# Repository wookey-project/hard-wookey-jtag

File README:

# WooKey JTAG Flasher PCB

## Introduction

Wookey | https://wookey-project.github.io/
Copyright 2018 The wookey project team <wookey@ssi.gouv.fr>

The Wookey from [ANSSI](https://www.ssi.gouv.fr) is an open source
hardware design, implementing an Encrypted Flash Drives.

This repository is aimed towards developers.

### Revision information

This directory contains the hardware design for the Wookey board, first public version (Wookey V2).

### PCB editing tools

All PCB files (schematic and PCB layout) have been designed using the KiCad EDA.
This Cross Platform and Open Source Electronics Design Automation Suite can be downloaded
on http://kicad-pcb.org/.

## Production files generation 101

### Configure the project

KiCad binaries location may change regarding your operating system.
This is why you have to set your environment.
This is done by sourcing the `setenv.sh` script. This script exports
all paths that are required in order to automaticaly generate the production files.

Most of the time, the paths proposed in this script are not the one you use in your specific installation.
The `setenv.sh` script support easy variables overloading by including a `setenv.local.sh` script file if this file exists in the same directory.
If you need to overload some of the variables of the `setenv.sh` script, just add them to your own `setenv.local.sh` file.
Here is an example to define KiCad environement path on Apple Mac OS.

```
  $ echo "export PYTHON_BIN_PATH = /Applications/KiCad/kicad.app/Contents/Frameworks/Python.framework/Versions/2.7/bin/python" > setenv.local.sh
  $ source setenv.sh
  Loading local SDK settings...
  =========================================================
  === Kicad environment configuration
  =========================================================
  PYTHON_BIN_PATH   = /Applications/KiCad/kicad.app/Contents/Frameworks/Python.framework/Versions/2.7/bin/python
  PYTHON_PATH     = /Applications/Kicad/kicad.app/Contents/Frameworks/python/site-packages
  BOM_GEN_PATH = /Applications/Kicad/kicad.app/Contents/SharedSupport/plugins/bom2grouped_csv.xsl
  TOOLS_PATH = ../../../tools
  =========================================================
```

The production files can be generated using the following command.

```
$ make
```

This will generate the production files in a new sub directory.
The directory name may differ according the project your are working with.

## PCB Pinout

## PCB Layers

### PCB TOP layer

### PCB BOTTOM layer

### Layers

Order and type of copper layers:
  TOP:  signal, front components
  GND:  ground plane
  PWR:  ground and power plane
  BOT:  signal, back components

### Stackup
4 layers, 1.6mm thickness
Outer layers 1 oz base copper foil
Inner layers 0.5 oz base copper foil

Electroless Nickel Immersion Gold (ENIG) surface finish

solder resist   0.0254mm
copper          0.0356mm    L1 (TOP)
FR408 prepreg   0.1702mm
copper          0.0178mm    L2 (GND)
FR408           1.1938mm
copper          0.0178mm    L3 (PWR)
FR408 prepreg   0.1702mm
copper          0.0356mm    L4 (BOT)
solder resist   0.0254mm

The substrate for both the core and prepreg is FR408,
with a dielectric constant of 3.66 at 1GHz.
The prepreg is comprised of 2 layers of Isola 2113.

## Regulatory compliance & handling

The Wookey board is intended for use as a development platform for hardware
or software. The board is an open system design, which does not include a
shielded enclosure. This may cause interference to other electrical or
electronic devices in close proximity. In a domestic environment, this product
may cause radio interference in which case the user may be required to take
adequate measures. In addition, this board should not be used near any medical
equipment or RF devices.

The board is sensitive to ESD. Hold the board only by its edges. After removing
the board from its box, place it on a grounded, static-free surface.

The board can become hot, like any fan-less design, during continuous high CPU
loads, mind its temperature while handling it.

## License

Wookey | https://wookey-project.github.io/
Copyright 2018 The wookey project team <wookey@ssi.gouv.fr>

This is an open hardware design licensed under the terms of the CERN Open
Hardware Licence (OHL) v1.2.

You may redistribute and modify this documentation under the terms of the CERN
OHL v.1.2 (http://ohwr.org/cernohl). This documentation is distributed WITHOUT
ANY EXPRESS OR IMPLIED WARRANTY, INCLUDING OF MERCHANTABILITY, SATISFACTORY
QUALITY AND FITNESS FOR A PARTICULAR PURPOSE. Please see the CERN OHL v.1.2 for
applicable conditions.

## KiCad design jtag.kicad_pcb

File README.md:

# WooKey JTAG Flasher PCB

## Introduction

Wookey | https://wookey-project.github.io/
Copyright 2018 ANSSI

Authors: The Wookey project Team <wookey@ssi.gouv.fr>

The Wookey from [ANSSI](https://www.ssi.gouv.fr) is an open source
hardware design, implementing an Encrypted Flash Drives.

This repository is aimed towards developers.

### Revision information

This directory contains the hardware design for the Wookey board, first public version (Wookey V2).

### PCB editing tools

All PCB files (schematic and PCB layout) have been designed using the KiCad EDA.
This Cross Platform and Open Source Electronics Design Automation Suite can be downloaded
on http://kicad-pcb.org/.

## Production files generation 101

### Configure the project

KiCad binaries location may change regarding your operating system.
This is why you have to set your environment.
This is done by sourcing the `setenv.sh` script. This script exports
all paths that are required in order to automaticaly generate the production files.

Most of the time, the paths proposed in this script are not the one you use in your specific installation.
The `setenv.sh` script support easy variables overloading by including a `setenv.local.sh` script file if this file exists in the same directory.
If you need to overload some of the variables of the `setenv.sh` script, just add them to your own `setenv.local.sh` file.
Here is an example to define KiCad environement path on Apple Mac OS.

```
  $ echo "export PYTHON_BIN_PATH = /Applications/KiCad/kicad.app/Contents/Frameworks/Python.framework/Versions/2.7/bin/python" > setenv.local.sh
  $ source setenv.sh
  Loading local SDK settings...
  =========================================================
  === Kicad environment configuration
  =========================================================
  PYTHON_BIN_PATH   = /Applications/KiCad/kicad.app/Contents/Frameworks/Python.framework/Versions/2.7/bin/python
  PYTHON_PATH     = /Applications/Kicad/kicad.app/Contents/Frameworks/python/site-packages
  BOM_GEN_PATH = /Applications/Kicad/kicad.app/Contents/SharedSupport/plugins/bom2grouped_csv.xsl
  TOOLS_PATH = ../../../tools
  =========================================================
```

The production files can be generated using the following command.

```
$ make
```

This will generate the production files in a new sub directory.
The directory name may differ according the project your are working with.

## PCB Pinout

## PCB Layers

### PCB TOP layer

### PCB BOTTOM layer

### Layers

Order and type of copper layers:
  TOP:  signal, front components
  GND:  ground plane
  PWR:  ground and power plane
  BOT:  signal, back components

### Stackup
4 layers, 1.6mm thickness
Outer layers 1 oz base copper foil
Inner layers 0.5 oz base copper foil

Electroless Nickel Immersion Gold (ENIG) surface finish

solder resist   0.0254mm
copper          0.0356mm    L1 (TOP)
FR408 prepreg   0.1702mm
copper          0.0178mm    L2 (GND)
FR408           1.1938mm
copper          0.0178mm    L3 (PWR)
FR408 prepreg   0.1702mm
copper          0.0356mm    L4 (BOT)
solder resist   0.0254mm

The substrate for both the core and prepreg is FR408,
with a dielectric constant of 3.66 at 1GHz.
The prepreg is comprised of 2 layers of Isola 2113.

## Regulatory compliance & handling

The Wookey board is intended for use as a development platform for hardware
or software. The board is an open system design, which does not include a
shielded enclosure. This may cause interference to other electrical or
electronic devices in close proximity. In a domestic environment, this product
may cause radio interference in which case the user may be required to take
adequate measures. In addition, this board should not be used near any medical
equipment or RF devices.

The board is sensitive to ESD. Hold the board only by its edges. After removing
the board from its box, place it on a grounded, static-free surface.

The board can become hot, like any fan-less design, during continuous high CPU
loads, mind its temperature while handling it.

## License

Wookey | https://wookey-project.github.io/
Copyright 2018 ANSSI

Authors: The Wookey project Team <wookey@ssi.gouv.fr>

This is an open hardware design licensed under the terms of the CERN Open
Hardware Licence (OHL) v1.2.

You may redistribute and modify this documentation under the terms of the CERN
OHL v.1.2 (http://ohwr.org/cernohl). This documentation is distributed WITHOUT
ANY EXPRESS OR IMPLIED WARRANTY, INCLUDING OF MERCHANTABILITY, SATISFACTORY
QUALITY AND FITNESS FOR A PARTICULAR PURPOSE. Please see the CERN OHL v.1.2 for
applicable conditions.

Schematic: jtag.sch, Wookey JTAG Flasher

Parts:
C9001, C9003: 10uF; C_0603_1608Metric; MFG Part Num TP8M106M6R3C
C9002, C9004, C9005, C9006, C9007, C9008, C9009, C9010, C9011, C9012, C9013, C9014: 100nF; C_0603_1608Metric; MFG Part Num GRM188R71H104KA93D
D9002: LED BLUE; LED_0603_1608Metric_Castellated; MFG Part Num VLMB1300-GS08
J9001: USB; USB_A_CNCTech_1001-011-01101_Horizontal
J9002: Conn_01x03; PinHeader_1x02_P2.54mm_Vertical
J9003: JTAG; PinHeader_2x05_P2.54mm_Horizontal
P9001: DEBUG/PROG; PinHeader_1x06_P2.54mm_Vertical; MFG Part Num 90120-0766
R9001, R9002, R9004: 10K; R_0603_1608Metric
R9003: 470; R_0603_1608Metric
SW9001: DFU; KSR_TACTILE_SWITCH; MFG Part Num KSR231G LFS
TP9001: MSWDIO; TestPoint_Pad_D1.0mm
TP9002: MSWCLK; TestPoint_Pad_D1.0mm
TP9003: +3V3; TestPoint_Pad_D1.0mm
TP9004: GND; TestPoint_Pad_D1.0mm
TP9005: CAN1_RX; TestPoint_Pad_D1.0mm
TP9006: CAN1_TX; TestPoint_Pad_D1.0mm
TP9007: CAN2_RX; TestPoint_Pad_D1.0mm
TP9008: CAN2_TX; TestPoint_Pad_D1.0mm
U9001: LD1117S33TR; SOT-223; MFG Part Num LD1117S33TR
U9002: STM32F105RBTx; LQFP-64_10x10mm_P0.5mm
U9003, U9004, U9005: 74LVCH2T45DC; VSSOP-8_2.3x2mm_P0.5mm

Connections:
+3V3: C9003.1, C9004.1, C9005.1, C9006.1, C9007.1, C9008.1, C9009.1, C9010.1, C9014.1, P9001.2, R9004.1, SW9001.1, TP9003.1, U9001.2 (VO), U9002.1 (VBAT), U9002.13 (VDDA), U9002.19 (VDD), U9002.32 (VDD), U9002.48 (VDD), U9002.64 (VDD), U9003.1 (VCCA), U9004.8 (VCCB), U9005.8 (VCCB)
+5V: C9001.1, C9002.1, J9001.1 (VBUS), U9001.3 (VI), U9002.42 (PA9)
/BOOT0: R9002.1, SW9001.2, U9002.60 (BOOT0)
/BOOT1: R9001.1, U9002.28 (PB2)
/CAN1_RX: TP9005.1, U9002.61 (PB8)
/CAN1_TX: TP9006.1, U9002.62 (PB9)
/CAN2_RX: TP9007.1, U9002.33 (PB12)
/CAN2_TX: TP9008.1, U9002.34 (PB13)
/JTAG_DIR: U9002.15 (PA1), U9003.5 (DIR), U9004.5 (DIR), U9005.5 (DIR)
/JTAG_NRESET: U9002.16 (PA2), U9004.6 (2B)
/JTAG_OUT_TCK: J9003.4 (SWDCLK/TCK), U9003.6 (2B)
/JTAG_OUT_TDI: J9003.8 (NC/TDI), U9004.2 (1A)
/JTAG_OUT_TDO: J9003.6 (SWO/TDO), U9005.2 (1A)
/JTAG_OUT_TMS: J9003.2 (SWDIO/TMS), U9003.7 (1B)
/JTAG_OUT_TRESET: J9003.10 (~RESET~), U9004.3 (2A)
/JTAG_TCK: U9002.21 (PA5), U9003.3 (2A)
/JTAG_TDI: U9002.17 (PA3), U9004.7 (1B)
/JTAG_TDO: U9002.22 (PA6), U9005.7 (1B)
/JTAG_TMS: U9002.20 (PA4), U9003.2 (1A)
/JTAG_VREF: C9011.1, C9012.1, C9013.1, J9003.1 (VCC), U9003.8 (VCCB), U9004.1 (VCCA), U9005.1 (VCCA)
/LED1: R9003.1, U9002.29 (PB10)
/MCU_SWCLK: TP9002.1, U9002.49 (PA14)
/MCU_SWDIO: TP9001.1, U9002.46 (PA13)
/NRST: P9001.3, R9004.2, U9002.7 (NRST)
/RX: J9002.1, U9002.59 (PB7)
/SWCLK: P9001.4, U9002.38 (PC7)
/SWDIO: P9001.5, U9002.39 (PC8)
/SWO: P9001.6, U9002.55 (PB3)
/TX: J9002.2, U9002.58 (PB6)
/USB_FS_D+: J9001.3 (D+), U9002.45 (PA12)
/USB_FS_D-: J9001.2 (D-), U9002.44 (PA11)
GND: C9001.2, C9002.2, C9003.2, C9004.2, C9005.2, C9006.2, C9007.2, C9008.2, C9009.2, C9010.2, C9011.2, C9012.2, C9013.2, C9014.2, D9002.1 (K), J9001.4 (GND), J9001.5 (Shield), J9003.3 (GND), J9003.5 (GND), J9003.9 (GNDDetect), P9001.1, R9001.2, R9002.2, TP9004.1, U9001.1 (GND), U9002.12 (VSSA), U9002.18 (VSS), U9002.31 (VSS), U9002.47 (VSS), U9002.63 (VSS), U9003.4 (GND), U9004.4 (GND), U9005.4 (GND), U9005.6 (2B)
unnamed: D9002.2 (A), R9003.2

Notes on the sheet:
BOOT MODE
LED
POWER
Boot0 (1-2) = 0 => Flash memory aliased at 0x0000000

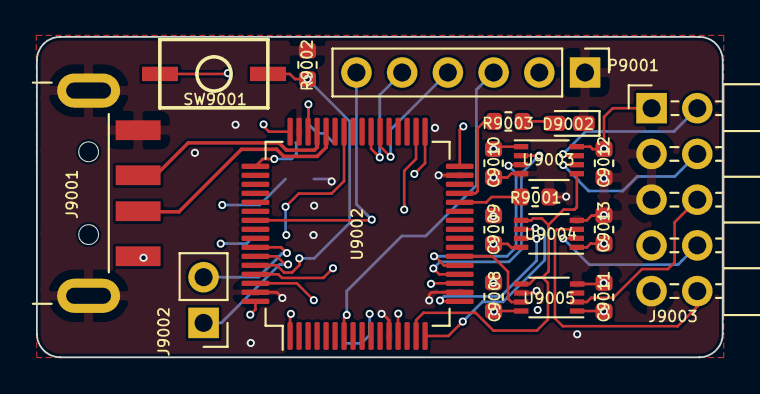
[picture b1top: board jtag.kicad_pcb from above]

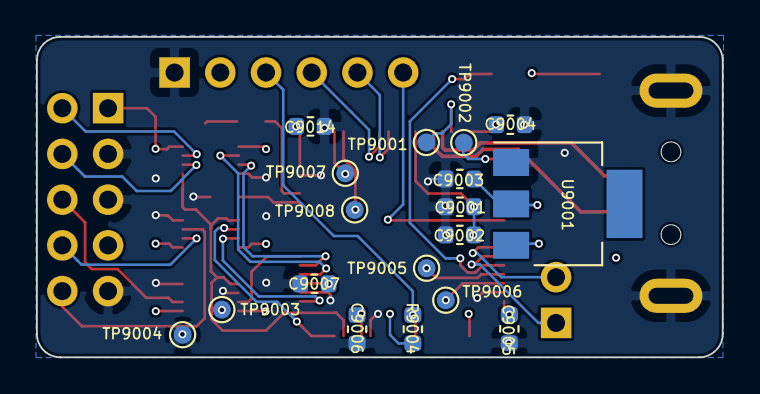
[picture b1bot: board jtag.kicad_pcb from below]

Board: 4 copper layers, 38.1 x 17.8 mm, 37 parts (18 on the bottom side), 33 nets.

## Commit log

2019-05-15 First import
2019-05-16 [enhancement] global cleanup
2019-05-16 [enhancement] add pcb screenshots
2019-05-16 [enhancement] move pcb screenshots to imgs directory
2019-05-16 [enhancement] Add LICENSE.txt
2019-05-16 [enhancement] Reference LICENSE in files
2019-05-16 [enhancement] General cleanup
2019-05-16 [enhancement] Add README and imgs files
2019-05-16 [enhancement] Update README and imgs
2019-05-17 [enhancement] Add setenv.local examples
2019-05-17 [fix] Rename files.
2019-08-26 [bugfix] copyright typo

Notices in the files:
jtag.kicad_pcb:
LICENCE: CERN Open Hardware Licence v1.2
